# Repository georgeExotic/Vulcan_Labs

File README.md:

# BLACK BETTY

Software for Black Betty, a Lab Testing Machine built Texas A&M University to characterize the pressure and desnity relationship of power bed for binder jetting AM development.

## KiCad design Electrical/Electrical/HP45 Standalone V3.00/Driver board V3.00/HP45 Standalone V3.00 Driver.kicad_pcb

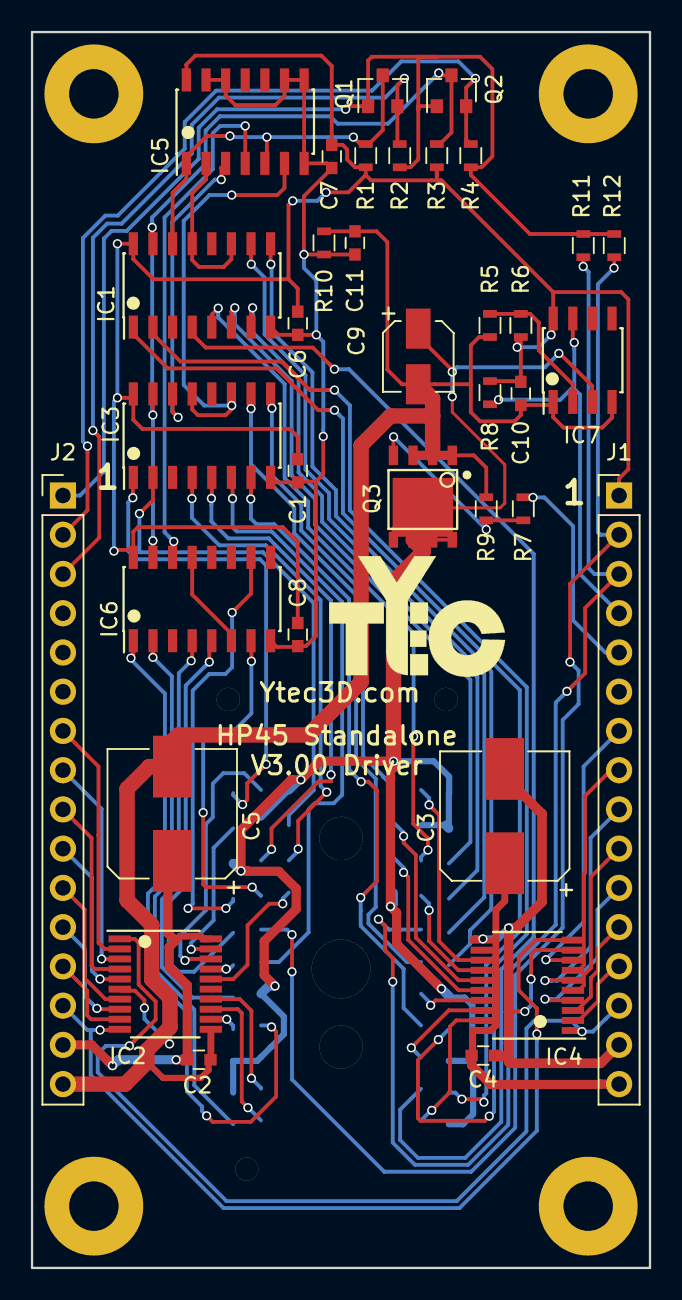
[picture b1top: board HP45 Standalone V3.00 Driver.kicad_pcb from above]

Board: 2 copper layers, 40.0 x 80.0 mm, 36 parts (1 on the bottom side), 73 nets.

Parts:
C1, C6, C7, C8, C10, C11: 0.1uF; C_0603
C2, C4: 1uF; C_0603
C3, C5: 100uF; CP_Elec_8x10
C9: 1uF; CP_Elec_4x5.8
Con1: HP45_connector; HP45_SMD_connector
IC1, IC3, IC6: HEF4017; SOIC-16_3.9x9.9mm_Pitch1.27mm
IC2, IC4: TLC59213; TSSOP-20_4.4x6.5mm_Pitch0.65mm
IC5: HCF4081; SOIC-14_3.9x8.7mm_Pitch1.27mm
IC7: LM311; SOIC-8_3.9x4.9mm_Pitch1.27mm
J1, J2: CONN_01X16; Socket_Strip_Straight_1x16_Pitch2.54mm
Q1, Q2: Q_NMOS_GSD; SOT-23
Q3: Q_NMOS_SGD; SO-8_PowerPAK
R1, R2, R3, R4, R9, R10: 2.2k; R_0603
R5: 1.2k; R_0603
R6, R8: 10k; R_0603
R7, R11, R12: 330; R_0603

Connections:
+3V3: J2.1, Q1.1, Q2.1, R2.2, R4.2, R11.2, R12.2
+12V: C1.1, C6.1, C7.1, C8.1, C10.1, IC1.16, IC3.16, IC5.14, IC6.16, IC7.8, J1.1, R1.2, R3.2, R6.1, R8.1
/ARST: IC1.15, IC3.15, IC6.15, Q2.3, R3.1
/C10X: Con1.28, J1.3, R11.1
/CACLK: J2.3, Q1.2, R2.1
/CARST: J2.2, Q2.2, R4.1
/CP00: IC2.4, J2.9
/CP01: IC4.4, J1.11
/CP02: IC2.9, J2.13
/CP03: IC4.3, J1.12
/CP04: IC2.7, J2.11
/CP05: IC4.2, J1.13
/CP06: IC2.8, J2.12
/CP07: IC4.8, J1.7
/CP08: IC2.3, J2.8
/CP09: IC4.6, J1.9
/CP10: IC2.2, J2.7
/CP11: IC4.5, J1.10
/CP12: IC2.5, J2.10
/CP13: IC4.7, J1.8
/CTSR: Con1.27, J1.2, R12.1
/HA00: Con1.25, IC6.5
/HA01: Con1.29, IC6.10
/HA02: Con1.23, IC3.6
/HA03: Con1.31, IC6.7
/HA04: Con1.17, IC6.4
/HA05: Con1.37, IC3.5
/HA06: Con1.15, IC6.1
/HA07: Con1.39, IC3.4
/HA08: Con1.1, IC6.2
/HA09: Con1.45, IC3.2
/HA10: Con1.6, IC1.1
/HA11: Con1.47, IC3.1
/HA12: Con1.8, IC1.4
/HA13: Con1.52, IC3.9
/HA14: Con1.14, IC1.2
/HA15: Con1.38, IC1.5
/HA16: Con1.16, IC3.7
/HA17: Con1.36, IC1.6
/HA18: Con1.22, IC1.9
/HA19: Con1.30, IC1.7
/HA20: Con1.24, IC3.10
/HA21: Con1.26, IC1.10
/HENA: J1.5, R7.2
/HGND: C9.1, Con1.2, Con1.5, Con1.9, Con1.10, Con1.11, Con1.18, Con1.19, Con1.34, Con1.35, Con1.42, Con1.43, Con1.44, Con1.48, Con1.51, IC7.3, Q3.3
/HP00: Con1.21, IC2.17
/HP01: Con1.20, IC4.17
/HP02: Con1.13, IC2.12
/HP03: Con1.12, IC4.18
/HP04: Con1.7, IC2.14
/HP05: Con1.4, IC4.19
/HP06: Con1.3, IC2.13
/HP07: Con1.50, IC4.13
/HP08: Con1.49, IC2.18
/HP09: Con1.46, IC4.15
/HP10: Con1.41, IC2.19
/HP11: Con1.40, IC4.16
/HP12: Con1.33, IC2.16
/HP13: Con1.32, IC4.14
/NCHECK: IC7.7, J1.4, R8.2
/PCLK: IC2.10, IC4.10, J2.14
/PCLR: IC2.1, IC4.1, J1.14
AGND: C1.2, C6.2, C7.2, C8.2, C11.1, IC1.8, IC3.8, IC5.7, IC5.8, IC5.9, IC5.12, IC5.13, IC6.8, R10.1
GND: C2.2, C3.2, C4.2, C5.2, C9.2, C10.2, C11.2, IC2.6, IC2.11, IC4.9, IC4.11, IC7.1, IC7.4, J1.15, J2.16, Q3.1, R5.2, R9.1, R10.2
unnamed: IC1.11, IC1.13, IC5.2
unnamed: IC1.14, IC5.1, IC5.5, Q1.3, R1.1
unnamed: IC3.11, IC3.13, IC5.6
unnamed: IC3.14, IC5.3
unnamed: IC5.4, IC6.14
unnamed: IC6.6, IC6.13
unnamed: IC7.2, R5.1, R6.2
unnamed: Q3.2, R7.1, R9.2
VHead: C2.1, C3.1, C4.1, C5.1, IC2.20, IC4.20, J1.16, J2.15

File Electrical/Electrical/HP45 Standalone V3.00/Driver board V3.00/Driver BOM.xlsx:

ref | value5 | footprint | lib | part
C1 | 0.1uF | Capacitors_SMD:C_0603 | device | C
C11 | 0.1uF | Capacitors_SMD:C_0603 | device | C
C10 | 0.1uF | Capacitors_SMD:C_0603 | device | C
C6 | 0.1uF | Capacitors_SMD:C_0603 | device | C
C8 | 0.1uF | Capacitors_SMD:C_0603 | device | C
C7 | 0.1uF | Capacitors_SMD:C_0603 | device | C
R5 | 1.2k | Resistors_SMD:R_0603 | device | R
C3 | 100uF | Capacitors_SMD:CP_Elec_8x10 | device | CP
C5 | 100uF | Capacitors_SMD:CP_Elec_8x10 | device | CP
R6 | 10k | Resistors_SMD:R_0603 | device | R
R8 | 10k | Resistors_SMD:R_0603 | device | R
C4 | 1uF | Capacitors_SMD:C_0603 | device | C
C9 | 1uF | Capacitors_SMD:CP_Elec_4x5.8 | device | CP
C2 | 1uF | Capacitors_SMD:C_0603 | device | C
R1 | 2.2k | Resistors_SMD:R_0603 | device | R
R2 | 2.2k | Resistors_SMD:R_0603 | device | R
R3 | 2.2k | Resistors_SMD:R_0603 | device | R
R4 | 2.2k | Resistors_SMD:R_0603 | device | R
R10 | 2.2k | Resistors_SMD:R_0603 | device | R
R9 | 2.2k | Resistors_SMD:R_0603 | device | R
R7 | 330 | Resistors_SMD:R_0603 | device | R
R11 | 330 | Resistors_SMD:R_0603 | device | R
R12 | 330 | Resistors_SMD:R_0603 | device | R
J1 | CONN_01X16 | Socket_Strips:Socket_Strip_Straight_1x16_Pitch2.54mm | conn | CONN_01X16
J2 | CONN_01X16 | Socket_Strips:Socket_Strip_Straight_1x16_Pitch2.54mm | conn | CONN_01X16
IC5 | HCF4081 | Housings_SOIC:SOIC-14_3.9x8.7mm_Pitch1.27mm | HP45 controller parts | HCF4081
IC1 | HEF4017 | Housings_SOIC:SOIC-16_3.9x9.9mm_Pitch1.27mm | HP45 controller parts | HEF4017
IC3 | HEF4017 | Housings_SOIC:SOIC-16_3.9x9.9mm_Pitch1.27mm | HP45 controller parts | HEF4017
IC6 | HEF4017 | Housings_SOIC:SOIC-16_3.9x9.9mm_Pitch1.27mm | HP45 controller parts | HEF4017
Con1 | HP45_connector | Electronics:HP45_SMD_connector | HP45 controller parts | HP45_connector
IC7 | LM311 | Housings_SOIC:SOIC-8_3.9x4.9mm_Pitch1.27mm | HP45 controller parts | LM311
Q2 | Q_NMOS_GSD | TO_SOT_Packages_SMD:SOT-23 | device | Q_NMOS_GSD
Q1 | Q_NMOS_GSD | TO_SOT_Packages_SMD:SOT-23 | device | Q_NMOS_GSD
Q3 | Q_NMOS_SGD | Electronics:SO-8_PowerPAK | device | Q_NMOS_SGD
IC2 | TLC59213 | Housings_SSOP:TSSOP-20_4.4x6.5mm_Pitch0.65mm | HP45 controller parts | TLC59213
IC4 | TLC59213 | Housings_SSOP:TSSOP-20_4.4x6.5mm_Pitch0.65mm | HP45 controller parts | TLC59213

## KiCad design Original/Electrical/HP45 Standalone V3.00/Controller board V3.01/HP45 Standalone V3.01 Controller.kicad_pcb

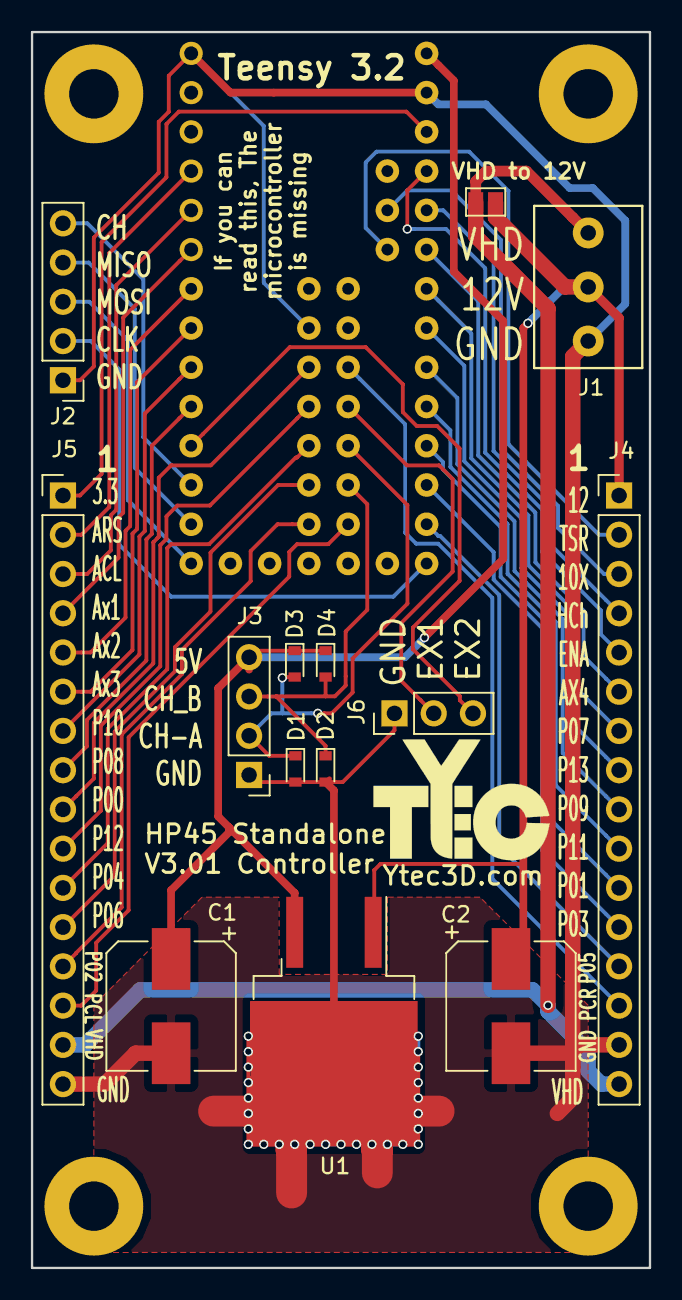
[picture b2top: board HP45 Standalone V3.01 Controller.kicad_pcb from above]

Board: 2 copper layers, 40.0 x 80.0 mm, 15 parts (0 on the bottom side), 39 nets.

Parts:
C1, C2: 100uF; CP_Elec_8x10
D1, D2, D3, D4: D; D_0603
J1: Screw_Terminal_1x03; 3.5mm_screw_terminal
J2: CONN_01X05; Socket_Strip_Straight_1x05_Pitch2.54mm
J3: CONN_01X04; Socket_Strip_Straight_1x04_Pitch2.54mm
J4, J5: CONN_01X16; Socket_Strip_Straight_1x16_Pitch2.54mm
J6: CONN_01X03; Socket_Strip_Straight_1x03_Pitch2.54mm
JP1: Jumper; GS2
U1: 7805; TO-263-2
uC1: Teensy_3.2_custom

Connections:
+3V3: J5.1, uC1.48
+5V: C1.1, D3.1, D4.1, J3.4, U1.3, uC1.50
+12V: C2.1, J1.2, J4.1, JP1.2, U1.1
/10X: J4.3, uC1.44
/ACLK: J5.3, uC1.5
/ARST: J5.2, uC1.4
/Aux1: J5.4, uC1.6
/Aux2: J5.5, uC1.7
/Aux3: J5.6, uC1.9
/Aux4: J4.6, uC1.43
/CH_A: D1.1, D3.2, J3.2, uC1.32
/CH_B: D2.1, D4.2, J3.3, uC1.30
/CS: J2.5, uC1.17
/Ext1: J6.2, uC1.34
/Ext2: J6.3, uC1.15
/HENA: J4.5, uC1.47
/MISO: J2.4, uC1.19
/MOSI: J2.3, uC1.21
/NCHECK: J4.4, uC1.45
/P00: J5.9, uC1.12
/P01: J4.11, uC1.33
/P02: J5.13, uC1.20
/P03: J4.12, uC1.31
/P04: J5.11, uC1.16
/P05: J4.13, uC1.29
/P06: J5.12, uC1.18
/P07: J4.7, uC1.41
/P08: J5.8, uC1.13
/P09: J4.9, uC1.37
/P10: J5.7, uC1.11
/P11: J4.10, uC1.35
/P12: J5.10, uC1.14
/P13: J4.8, uC1.39
/PCLK: J5.14, uC1.28
/PCLR: J4.14, uC1.36
/SCLK: J2.2, uC1.27
/TSR: J4.2, uC1.42
GND: C1.2, C2.2, D1.2, D2.2, J1.1, J2.1, J3.1, J4.15, J5.16, J6.1, U1.2, uC1.1, uC1.10, uC1.49
VHEAD: J1.3, J4.16, J5.15, JP1.1

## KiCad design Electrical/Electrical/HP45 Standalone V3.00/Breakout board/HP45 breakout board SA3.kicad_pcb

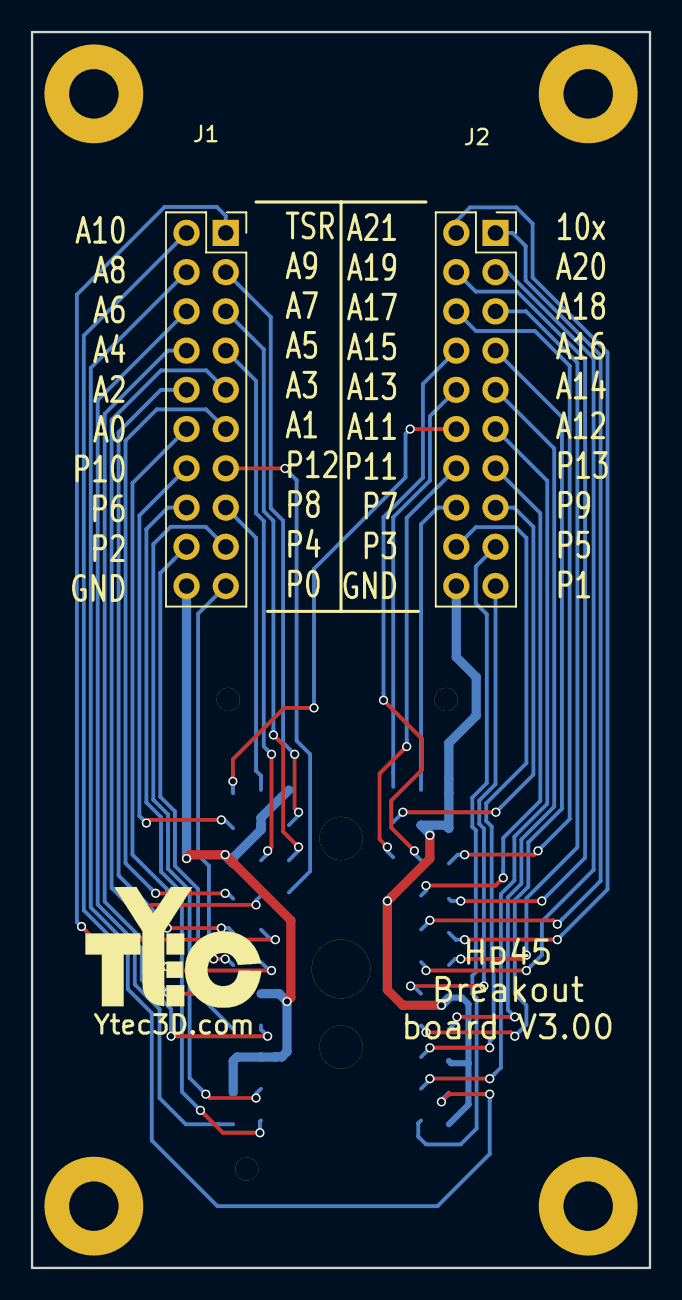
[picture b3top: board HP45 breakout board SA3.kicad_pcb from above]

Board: 2 copper layers, 40.0 x 80.0 mm, 3 parts (1 on the bottom side), 39 nets.

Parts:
Con1: HP45_connector; HP45_SMD_connector
J1, J2: CONN_02X10; Socket_Strip_Straight_2x10_Pitch2.54mm

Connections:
/10X: Con1.28, J2.1
/A0: Con1.25, J1.12
/A1: Con1.29, J1.11
/A2: Con1.23, J1.10
/A3: Con1.31, J1.9
/A4: Con1.17, J1.8
/A5: Con1.37, J1.7
/A6: Con1.15, J1.6
/A7: Con1.39, J1.5
/A8: Con1.1, J1.4
/A9: Con1.45, J1.3
/A10: Con1.6, J1.2
/A11: Con1.47, J2.12
/A12: Con1.8, J2.11
/A13: Con1.52, J2.10
/A14: Con1.14, J2.9
/A15: Con1.38, J2.8
/A16: Con1.16, J2.7
/A17: Con1.36, J2.6
/A18: Con1.22, J2.5
/A19: Con1.30, J2.4
/A20: Con1.24, J2.3
/A21: Con1.26, J2.2
/HGND: Con1.2, Con1.5, Con1.9, Con1.10, Con1.11, Con1.18, Con1.19, Con1.34, Con1.35, Con1.42, Con1.43, Con1.44, Con1.48, Con1.51, J1.20, J2.20
/P0: Con1.21, J1.19
/P1: Con1.20, J2.19
/P2: Con1.13, J1.18
/P3: Con1.12, J2.18
/P4: Con1.7, J1.17
/P5: Con1.4, J2.17
/P6: Con1.3, J1.16
/P7: Con1.50, J2.16
/P8: Con1.49, J1.15
/P9: Con1.46, J2.15
/P10: Con1.41, J1.14
/P11: Con1.40, J2.14
/P12: Con1.33, J1.13
/P13: Con1.32, J2.13
/TSR: Con1.27, J1.1

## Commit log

2020-02-08 ORIGINAL VERSION
2020-02-11 TEST
2020-02-12 Original State
2020-02-12 Erase
2020-02-12 Create Software
2020-02-12 Uploading Original Reposatory
    Firmware
    Software
2020-02-12 Original Files
2020-02-12 Set theme jekyll-theme-slate
2020-02-20 Updated Homing condition
    Changed flag from 0 to 1 to simulate that homing has finished
2020-02-24 Manually imported path
2020-02-24 never mind the last commit(JORGE)
2020-03-03 Working new Mac
2020-04-13 GUI update
    4/13
2020-04-18 cool
2020-08-31 update 420 folder
2020-09-04 clone hx711
2020-09-05 Added GUI components in python format
2020-09-05 Updated Code to Display GUI
2020-09-05 Added refresh rate of 1fps to GUI
2020-09-06 size adjustments to some components
2020-09-06 resizing and comments on GUI components
2020-09-07 Resized GUI components
2020-09-07 Realligned GUI elements, added Logo, added Icon
2020-09-09 GUI can read force / updated GUI
2020-09-15 Added comments
2020-09-15 sponsor demo
2020-09-15 alex check
2020-09-15 every one on the same page
2020-09-15 fixed merge err
2020-09-15 erase stuff
2020-09-16 GUI working faster and calibrate first steps
2020-09-16 Added calibration messages and global variables
2020-09-16 Added Calibration Menu Chain
2020-09-16 Program buttons now update state of system
2020-09-17 changed calibration to calibrate
2020-09-17 so far
2020-09-17 calibration Procedure completed - missing window inbetween
2020-09-19 added threading option and updated current pressure display
2020-09-20 Updated desired pressure reading
2020-09-23 added tare button
2020-09-23 tare working
2020-09-27 Clicking jog up will plot force data from database
2020-09-28 messing with stylesheets
2020-09-28 UI updates
2020-09-28 old logo
2020-09-28 examples
2020-09-28 jog up to graph
2020-09-28 added plotting to GUI
2020-10-03 demoPDR
2020-10-03 updated plotting
2020-10-03 mqtt class
2020-10-03 Organized file structure
2020-10-07 motor modbus client class
2020-10-14 check modbus connection
2020-10-15 connected jog buttons to modbus.py
2020-10-17 writting succ
2020-10-17 alot of stuff working
2020-10-17 adding comments
2020-10-18 changed jog down to use MA and POS
2020-10-18 some more funcs
2020-10-19 ccw working
2020-10-21 update load cell
2020-10-21 commented out stuff
2020-10-26 testing plotting methods
2020-10-26 plot live data and added data table
2020-10-26 added limit switch class
2020-10-26 torque testing
2020-10-29 added pressure plot to live plotting
2020-11-02 export function
2020-11-02 plotting and export
2020-11-02 export data to USB
2020-11-05 added disabling for mode selection
2020-11-05 readjusted GUI
2020-11-05 did things
2020-11-05 testing load cell
2020-11-09 from pi
2020-11-09 moving it for the first time
2020-11-11 updated a lot on control
2020-11-11 time to sleep
2020-11-12 limit swtich for home
2020-11-13 homing done
2020-11-14 GUI updates motor class params from user input params with default values of zero.
2020-11-16 GUI -> GUI Pro S Deluxe
2020-11-17 commited changes from pi
2020-11-17 modifcations from testing
2020-11-18 added keyboard to GUI
2020-11-18 adjustments
2020-11-18 close call
2020-11-18 Dickson demo
2020-11-22 cleaning up
2020-11-22 organizing a bit
2020-11-22 almost home
2020-11-23 about to be a long night
2020-11-23 missing loadcell when running
2021-02-27 init original
2021-02-27 integrated threading for force reading
2021-02-28 before chao
2021-03-11 clean up.. everything else moved to /Vulcan_Lbas/.other
2021-03-14 threading functionality for jogging up and homing Co-authored-by: atrejos <alextre.edu@gmail.com>
2021-03-14 finish testing for negative vals
2021-03-14 its fucking going down
2021-03-17 jorge going at it
2021-03-19 jogging and homing revamp Co-authored-by: roaj <roaj@tamu.edu>
2021-03-19 jogging and homing update Co-authored-by: jorge roa <roaj@tamu.edu>
2021-03-19 updates.
2021-04-02 ay vamos-antes del helado
2021-04-22 test setup
2021-04-22 thread testing platform
2021-04-22 testing updates
2021-04-23 narrowing down the error
2021-04-27 testing new gui
2021-04-27 updated new gui
2021-04-30 updates to tempfile
2021-05-01 added locks to ensure read and write modbus commands are mutually exclusive
2021-05-01 added data sensetizing to run function and a popup alerting powder is needed
2021-05-04 added data export functionality with file path input and sqlite database
2021-05-06 run function
2021-05-14 increased sampling rate and slowed run motions in profiles
2021-05-15 working on loadcell.py
2021-05-16 added new run popups
2021-05-17 to the lab
2022-02-06 02_05
